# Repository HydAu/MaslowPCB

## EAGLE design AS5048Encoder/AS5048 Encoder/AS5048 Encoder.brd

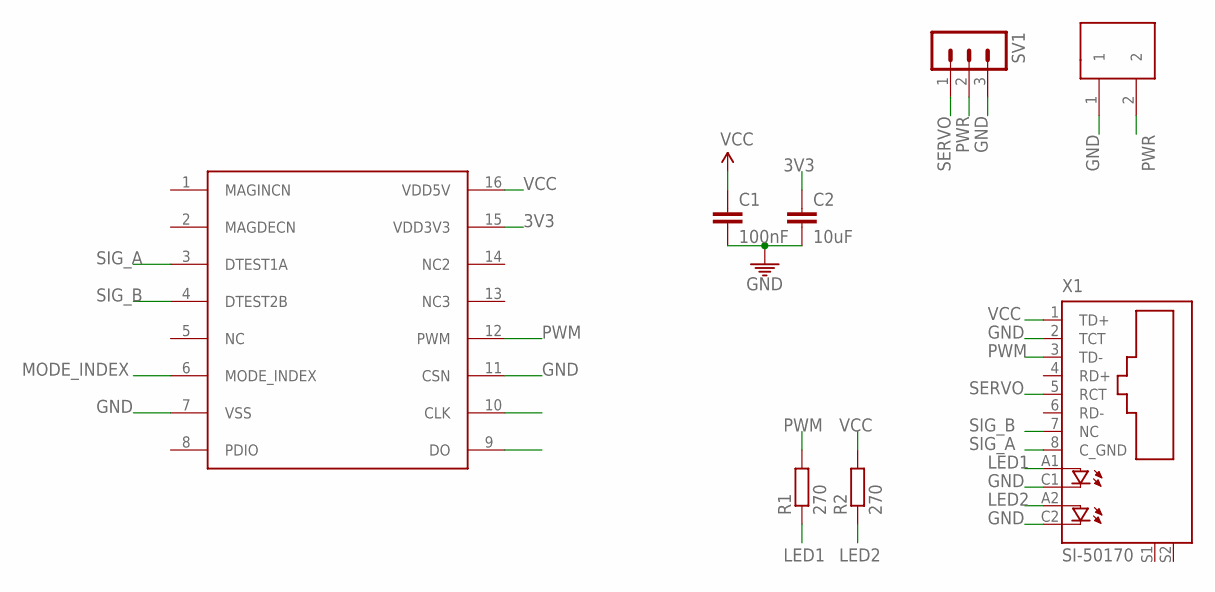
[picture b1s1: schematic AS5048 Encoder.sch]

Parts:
C1: 100nF; C0805
C2: 10uF; C0805
R1, R2: 270; R0805
SV1: MA03-1
U$1: TERMINALBLOCK277-1667-ND
U$2: AS5145; SSOP16
X1: SI-50170

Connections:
3V3: C2.1, U$2.15 (VDD3V3)
GND: C1.2, C2.2, SV1.3, U$1.1, U$2.7 (VSS), U$2.11 (CSN), X1.2 (TCT), X1.C1 (C), X1.C2 (C1)
LED1: R1.1, X1.A1 (A)
LED2: R2.1, X1.A2 (A1)
MODE_INDEX: U$2.6 (MODE_INDEX)
PWM: R1.2, U$2.12 (PWM), X1.3 (TD-)
PWR: SV1.2, U$1.2
SERVO: SV1.1, X1.5 (RCT)
SIG_A: U$2.3 (DTEST1A), X1.8 (C_GND)
SIG_B: U$2.4 (DTEST2B), X1.7 (NC)
VCC: C1.1, R2.2, U$2.16 (VDD5V), X1.1 (TD+)

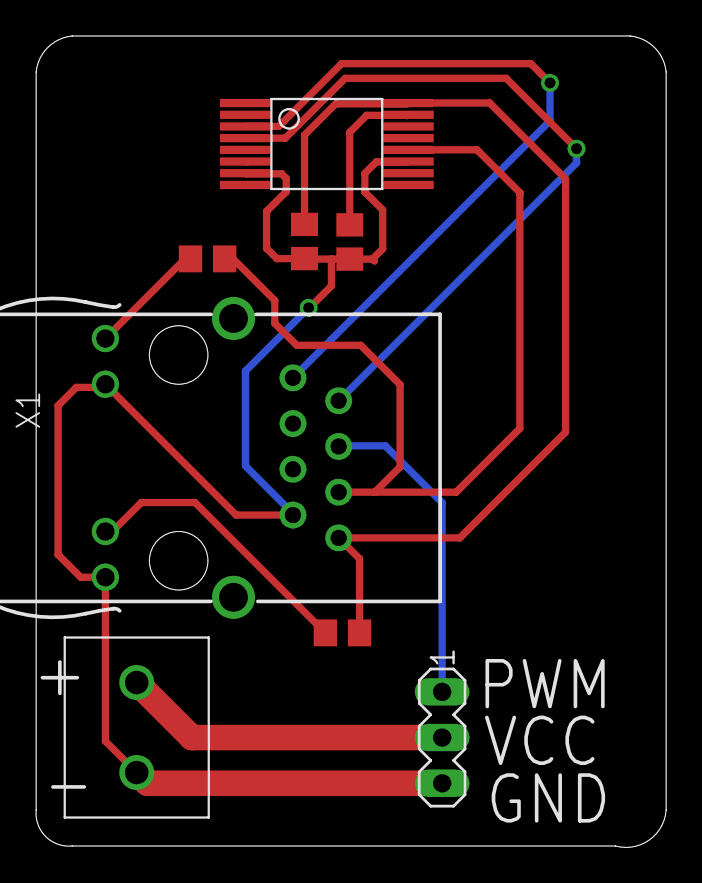
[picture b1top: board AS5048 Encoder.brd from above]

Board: 2 copper layers, 35.0 x 45.1 mm, 8 parts (0 on the bottom side), 10 nets.

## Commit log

2016-07-23 last before new chip
2016-07-23 added missing dimension
2016-07-23 added library
2016-07-23 all parts in place
2016-07-23 board looks done?
2016-07-23 routed mode
2016-07-23 shipped here
2016-08-13 added ground connection
2016-08-13 closed eagle
2016-08-13 cns low
2016-08-14 total revamp of encoder board
2016-08-15 reroute and move around
2016-08-19 commit to change branches
2016-08-20 add todo list

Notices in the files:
parts and their libraries:
SparkFun-Aesthetics: Licensing: CC v3.0 Share-Alike You are welcome to use this library for commercial purposes.
